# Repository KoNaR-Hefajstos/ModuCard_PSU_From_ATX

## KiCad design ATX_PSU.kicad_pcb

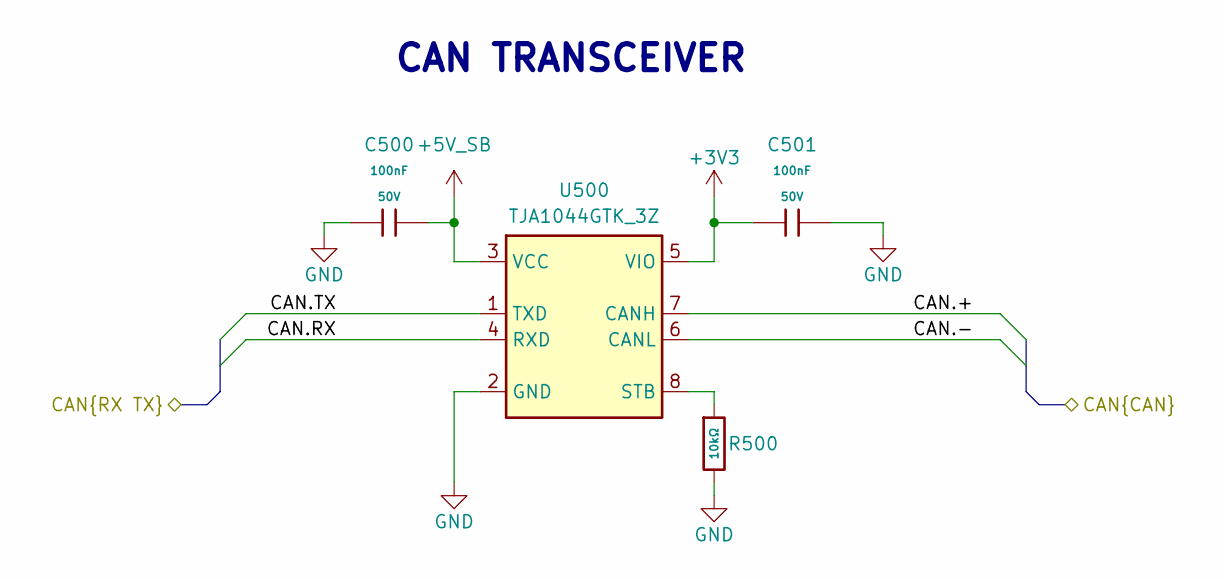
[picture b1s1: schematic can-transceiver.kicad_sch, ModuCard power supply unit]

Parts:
C500, C501: 100nF; C_0402; Voltage Rated 50V; Tolerance ±10%; Part CL05B104KB54PNC; LCSC C307331
R500: 10kΩ; R_0402; Overload Voltage (Max) 50V; Tolerance ±1%; Part 0402WGF1002TCE; LCSC C25744
U500: TJA1044GTK_3Z; HVSON-8-1EP_3x3mm_P0.65mm_EP1.6x2.4mm; Manufacturer_Part_Number TJA1044GTK/3Z; LCSC C5215851

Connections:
+3V3: C501.1, U500.5 (VIO); also elsewhere on the board
+5V_SB: C500.2, U500.3 (VCC); also elsewhere on the board
/Backplane/CAN1.+: U500.7 (CANH); also elsewhere on the board
/Backplane/CAN1.-: U500.6 (CANL); also elsewhere on the board
/CAN transceiver 1/CAN.RX: U500.4 (RXD); also elsewhere on the board
/CAN transceiver 1/CAN.TX: U500.1 (TXD); also elsewhere on the board
GND: C500.1, C501.2, R500.2, U500.2 (GND), U500.9 (EP); also elsewhere on the board
unnamed: R500.1, U500.8 (STB)

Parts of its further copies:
C600, C601: 100nF; C_0402; Voltage Rated 50V; Tolerance ±10%; Part CL05B104KB54PNC; LCSC C307331
R600: 10kΩ; R_0402; Overload Voltage (Max) 50V; Tolerance ±1%; Part 0402WGF1002TCE; LCSC C25744
U600: TJA1044GTK_3Z; HVSON-8-1EP_3x3mm_P0.65mm_EP1.6x2.4mm; Manufacturer_Part_Number TJA1044GTK/3Z; LCSC C5215851

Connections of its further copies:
+3V3: C601.1, U600.5 (VIO); also elsewhere on the board
+5V_SB: C600.2, U600.3 (VCC); also elsewhere on the board
/Backplane/CAN2.+: U600.7 (CANH); also elsewhere on the board
/Backplane/CAN2.-: U600.6 (CANL); also elsewhere on the board
/CAN transceiver 2/CAN.RX: U600.4 (RXD); also elsewhere on the board
/CAN transceiver 2/CAN.TX: U600.1 (TXD); also elsewhere on the board
GND: C600.1, C601.2, R600.2, U600.2 (GND), U600.9 (EP); also elsewhere on the board
unnamed: R600.1, U600.8 (STB)

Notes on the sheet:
CAN TRANSCEIVER

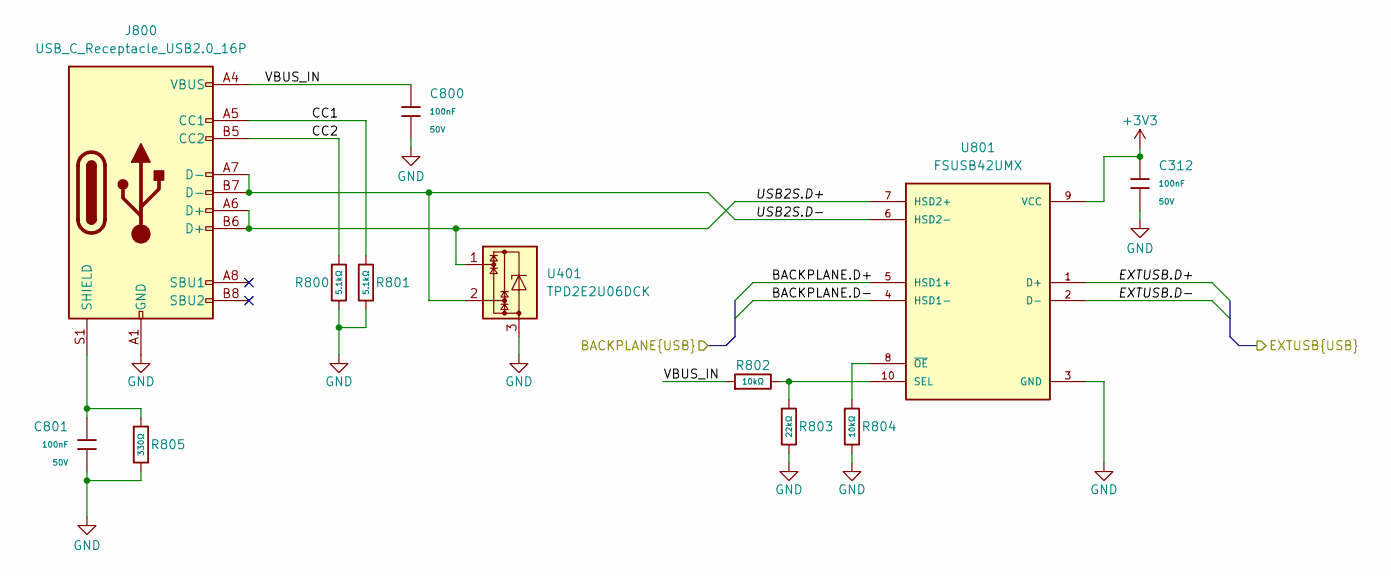
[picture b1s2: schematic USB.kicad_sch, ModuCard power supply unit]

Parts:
C312, C800, C801: 100nF; C_0402; Voltage Rated 50V; Tolerance ±10%; Part CL05B104KB54PNC; LCSC C307331
J800: USB_C_Receptacle_USB2.0_16P; USB_C_Receptacle_GCT_USB4105-xx-A_16P_TopMnt_Horizontal
R800, R801: 5.1kΩ; R_0402; Overload Voltage (Max) 50V; Tolerance ±1%; Part 0402WGF5101TCE; LCSC C25905
R802, R804: 10kΩ; R_0402; Overload Voltage (Max) 50V; Tolerance ±1%; Part 0402WGF1002TCE; LCSC C25744
R803: 22kΩ; R_0402; Overload Voltage (Max) 50V; Tolerance ±1%; Part 0402WGF2202TCE; LCSC C25768
R805: 330Ω; R_0402; Overload Voltage (Max) 50V; Tolerance ±1%; Part 0402WGF3300TCE; LCSC C25104
U401: TPD2E2U06DCK; SOT-323_SC-70; LCSC C5350871
U801: FSUSB42UMX; UFQFN-10_1.4x1.8; PARTREV 1.25; LCSC C49186231

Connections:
+3V3: C312.1, U801.9 (VCC); also elsewhere on the board
/Backplane/BACKPLANE.D+: U801.5 (HSD1+); also elsewhere on the board
/Backplane/BACKPLANE.D-: U801.4 (HSD1-); also elsewhere on the board
/USB-hub/USBIN1.D+: U801.1 (D+); also elsewhere on the board
/USB-hub/USBIN1.D-: U801.2 (D-); also elsewhere on the board
/USB/CC1: J800.A5 (CC1), R801.1
/USB/CC2: J800.B5 (CC2), R800.1
/USB/USB2S.D+: J800.A6 (D+), J800.B6 (D+), U401.1, U801.7 (HSD2+)
/USB/USB2S.D-: J800.A7 (D-), J800.B7 (D-), U401.2, U801.6 (HSD2-)
/USB/VBUS_IN: C800.1, J800.A4 (VBUS), J800.A9 (VBUS), J800.B4 (VBUS), J800.B9 (VBUS), R802.1
GND: C312.2, C800.2, C801.2, J800.A1 (GND), J800.A12 (GND), J800.B1 (GND), J800.B12 (GND), R800.2, R801.2, R803.2, R804.2, R805.2, U401.3, U801.3 (GND); also elsewhere on the board
unnamed: C801.1, J800.S1 (SHIELD), R805.1
unnamed: R802.2, R803.1, U801.10 (SEL)
unnamed: R804.1, U801.8 (~OE)

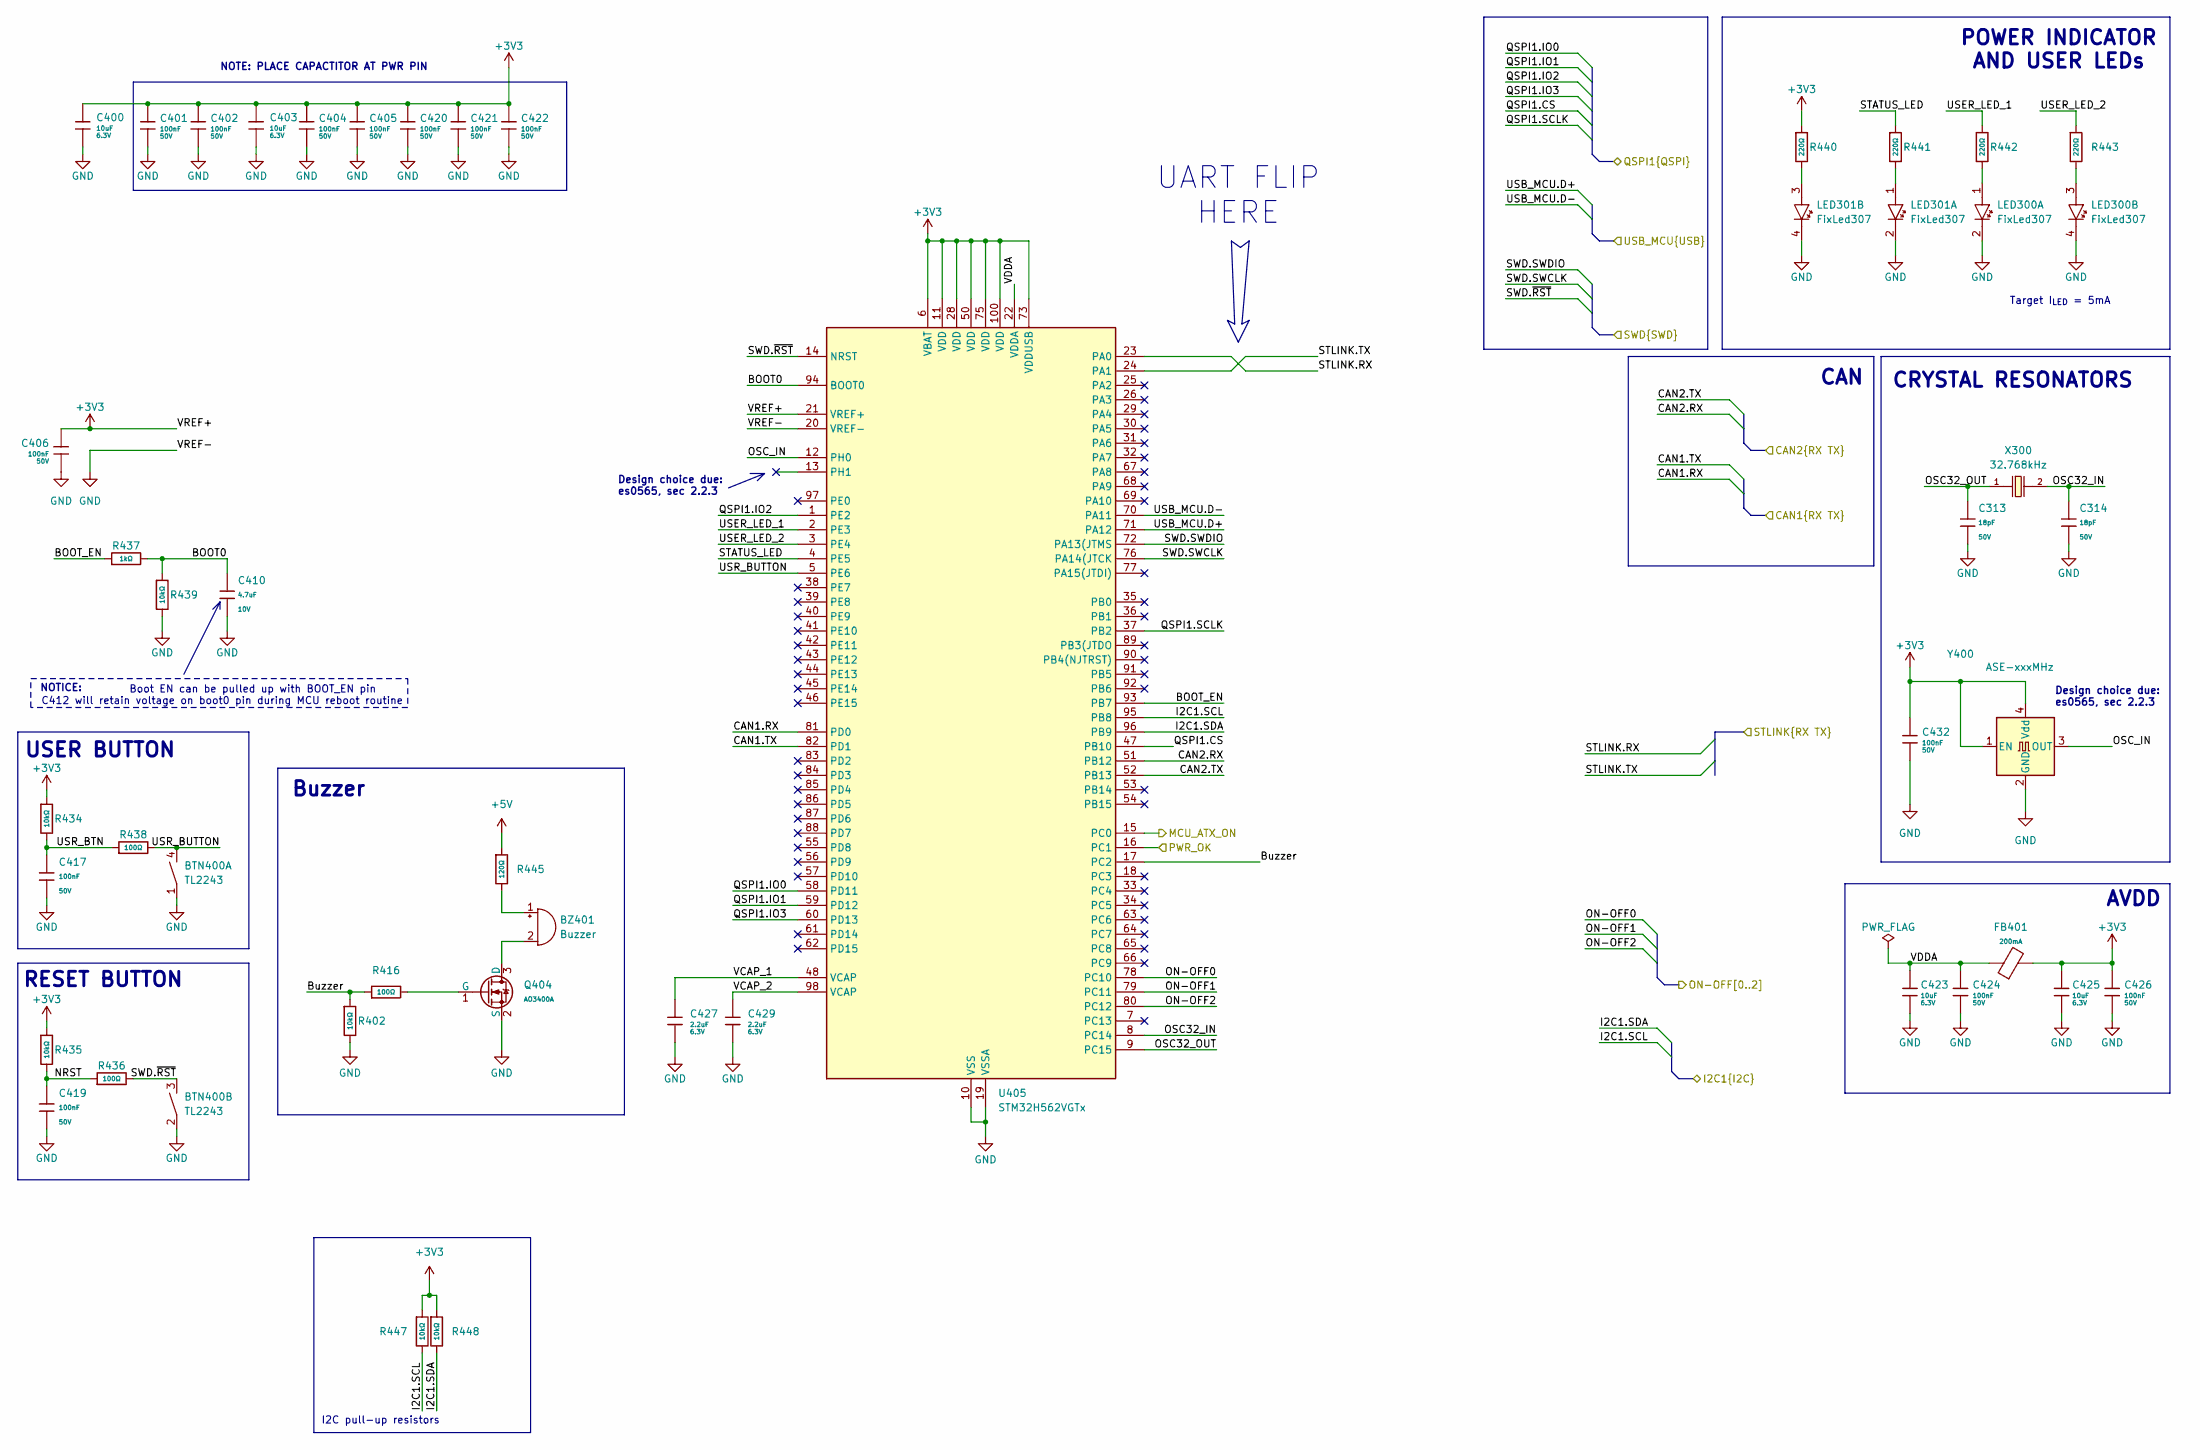
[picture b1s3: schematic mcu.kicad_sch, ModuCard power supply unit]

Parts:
BTN400: TL2243
BZ401: Buzzer; BUZ-TH_BD12.0-P7.60-D0.6-FD
C313, C314: 18pF; C_0402; Voltage Rated 50V; Tolerance ±5%; Part 0402CG180J500NT; LCSC C1549
C400, C403, C423, C425: 10uF; C_0402; Voltage Rated 6.3V; Tolerance ±20%; Part CL05A106MQ5NUNC; LCSC C15525
C401, C402, C404, C405, C406, C417, C419, C420, C421, C422, C424, C426, C432: 100nF; C_0402; Voltage Rated 50V; Tolerance ±10%; Part CL05B104KB54PNC; LCSC C307331
C410: 4.7uF; C_0402; Voltage Rated 10V; Tolerance ±20%; Part CL05A475MP5NRNC; LCSC C23733
C427, C429: 2.2uF; C_0402; Voltage Rated 6.3V; Tolerance ±20%; Part CL05A225MQ5NSNC; LCSC C12530
FB401: FB_0603; Current Rating 200mA; Tolerance ±25%; Part GZ1608D601TF; LCSC C1002
LED300, LED301: FixLed307
Q404: AO3400A; Q_SOT-23; Part AO3400A; LCSC C20917
R402, R434, R435, R439, R447, R448: 10kΩ; R_0402; Overload Voltage (Max) 50V; Tolerance ±1%; Part 0402WGF1002TCE; LCSC C25744
R416: 100Ω; R_0603; Overload Voltage (Max) 75V; Tolerance ±1%; Part 0603WAF1000T5E; LCSC C22775
R436, R438: 100Ω; R_0402; Overload Voltage (Max) 50V; Tolerance ±1%; Part 0402WGF1000TCE; LCSC C25076
R437: 1kΩ; R_0402; Overload Voltage (Max) 50V; Tolerance ±1%; Part 0402WGF1001TCE; LCSC C11702
R440, R441, R442, R443: 220Ω; R_0402; Overload Voltage (Max) 50V; Tolerance ±1%; Part 0402WGF2200TCE; LCSC C25091
R445: 120Ω; R_0402; Overload Voltage (Max) 50V; Tolerance ±1%; Part 0402WGF1200TCE; LCSC C25079
U405: STM32H562VGTx; LQFP-100_14x14mm_P0.5mm
X300: Q13FC1350000400; FC-135R_L3.2-W1.5; Frequency Tolerance ±20ppm; Part Q13FC13500004; LCSC C32346
Y400: ASE-xxxMHz; Oscillator_SMD_Abracon_ASE-4Pin_3.2x2.5mm; MPN OT322512MJBA4SL; LCSC C725989

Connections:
+3V3: C400.1, C401.1, C402.1, C403.1, C404.1, C405.1, C406.1, C420.1, C421.1, C422.1, C425.1, C426.1, C432.1, FB401.2, R434.1, R435.1, R440.1, R447.1, R448.1, U405.6 (VBAT), U405.11 (VDD), U405.21 (VREF+), U405.28 (VDD), U405.50 (VDD), U405.73 (VDDUSB), U405.75 (VDD), U405.100 (VDD), Y400.1 (EN), Y400.4 (Vdd); also elsewhere on the board
+5V: R445.1; also elsewhere on the board
/ATX connector/PWR_OK_ATX: U405.16 (PC1); also elsewhere on the board
/CAN transceiver 1/CAN.RX: U405.81 (PD0); also elsewhere on the board
/CAN transceiver 1/CAN.TX: U405.82 (PD1); also elsewhere on the board
/CAN transceiver 2/CAN.RX: U405.51 (PB12); also elsewhere on the board
/CAN transceiver 2/CAN.TX: U405.52 (PB13); also elsewhere on the board
/MCU/BOOT0: C410.1, R437.2, R439.1, U405.94 (BOOT0)
/MCU/BOOT_EN: R437.1, U405.93 (PB7)
/MCU/Buzzer: R402.1, R416.1, U405.17 (PC2)
/MCU/I2C1.SCL: R447.2, U405.95 (PB8); also elsewhere on the board
/MCU/I2C1.SDA: R448.2, U405.96 (PB9); also elsewhere on the board
/MCU/MCU_ATX_ON: U405.15 (PC0); also elsewhere on the board
/MCU/NRST: C419.1, R435.2, R436.1
/MCU/ON-OFF0: U405.78 (PC10); also elsewhere on the board
/MCU/ON-OFF1: U405.79 (PC11); also elsewhere on the board
/MCU/ON-OFF2: U405.80 (PC12); also elsewhere on the board
/MCU/OSC32_IN: C314.1, U405.8 (PC14), X300.2
/MCU/OSC32_OUT: C313.1, U405.9 (PC15), X300.1
/MCU/OSC_IN: U405.12 (PH0), Y400.3 (OUT)
/MCU/QSPI1.CS: U405.47 (PB10); also elsewhere on the board
/MCU/QSPI1.IO0: U405.58 (PD11); also elsewhere on the board
/MCU/QSPI1.IO1: U405.59 (PD12); also elsewhere on the board
/MCU/QSPI1.IO2: U405.1 (PE2); also elsewhere on the board
/MCU/QSPI1.IO3: U405.60 (PD13); also elsewhere on the board
/MCU/QSPI1.SCLK: U405.37 (PB2); also elsewhere on the board
/MCU/STATUS_LED: R441.1, U405.4 (PE5)
/MCU/STLINK.RX: U405.23 (PA0); also elsewhere on the board
/MCU/STLINK.TX: U405.24 (PA1); also elsewhere on the board
/MCU/SWD.SWCLK: U405.76 (PA14(JTCK); also elsewhere on the board
/MCU/SWD.SWDIO: U405.72 (PA13(JTMS); also elsewhere on the board
/MCU/SWD.~RST: BTN400.3, R436.2, U405.14 (NRST); also elsewhere on the board
/MCU/USB_MCU.D+: U405.71 (PA12); also elsewhere on the board
/MCU/USB_MCU.D-: U405.70 (PA11); also elsewhere on the board
/MCU/USER_LED_1: R442.1, U405.2 (PE3)
/MCU/USER_LED_2: R443.1, U405.3 (PE4)
/MCU/USR_BTN: C417.1, R434.2, R438.1
/MCU/USR_BUTTON: BTN400.4, R438.2, U405.5 (PE6)
/MCU/VCAP_1: C427.1, U405.48 (VCAP)
/MCU/VCAP_2: C429.1, U405.98 (VCAP)
/MCU/VDDA: C423.1, C424.1, FB401.1, U405.22 (VDDA)
GND: BTN400.1, BTN400.2, C313.2, C314.2, C400.2, C401.2, C402.2, C403.2, C404.2, C405.2, C406.2, C410.2, C417.2, C419.2, C420.2, C421.2, C422.2, C423.2, C424.2, C425.2, C426.2, C427.2, C429.2, C432.2, LED300.2, LED300.4, LED301.2, LED301.4, Q404.2 (S), R402.2, R439.2, U405.10 (VSS), U405.19 (VSSA), U405.20 (VREF-), U405.27 (VSS), U405.49 (VSS), U405.74 (VSS), U405.99 (VSS), Y400.2 (GND); also elsewhere on the board
unnamed: BZ401.1 (+), R445.2
unnamed: BZ401.2 (-), Q404.3 (D)
unnamed: LED300.1, R442.2
unnamed: LED300.3, R443.2
unnamed: LED301.1, R441.2
unnamed: LED301.3, R440.2
unnamed: Q404.1 (G), R416.2

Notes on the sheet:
Design choice due: es0565, sec 2.2.3
USER BUTTON
AVDD
CRYSTAL RESONATORS
RESET BUTTON
Buzzer
NOTICE:
POWER INDICATOR AND USER LEDs
Target I_{LED} = 5mA
I2C pull-up resistors
CAN
Boot EN can be pulled up with BOOT_EN pin C412 will retain voltage on boot0 pin during MCU reboot routine
UART FLIP HERE
NOTE: PLACE CAPACTITOR AT PWR PIN

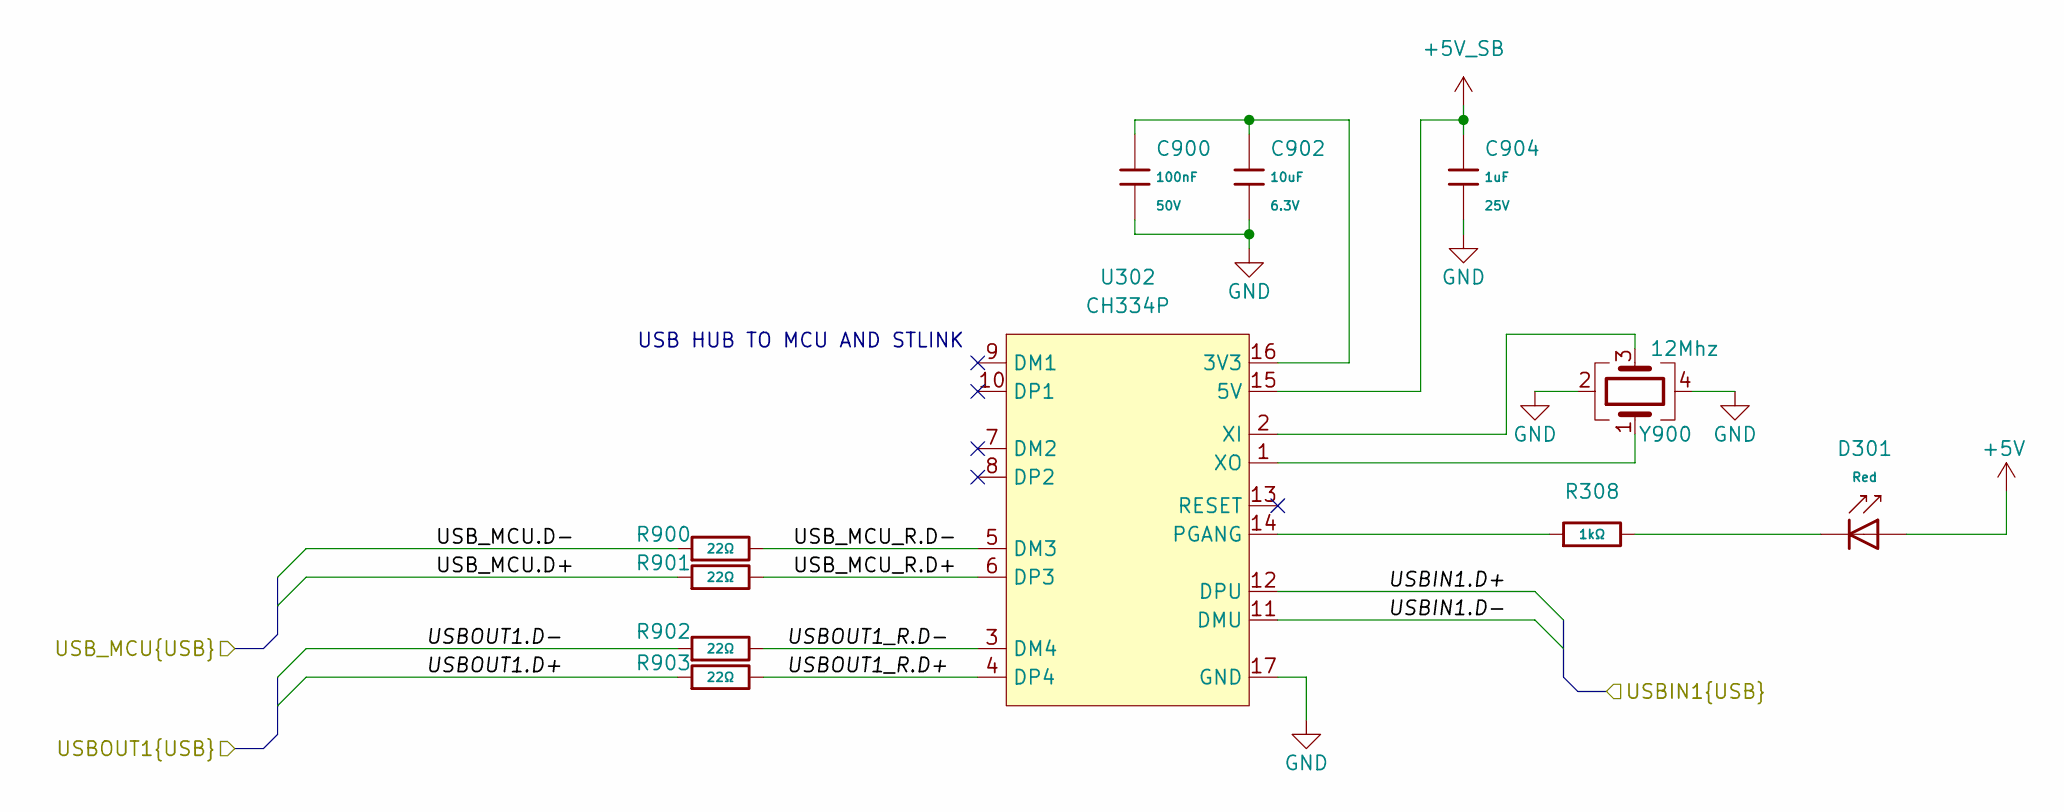
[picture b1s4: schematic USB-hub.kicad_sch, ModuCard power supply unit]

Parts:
C900: 100nF; C_0402; Voltage Rated 50V; Tolerance ±10%; Part CL05B104KB54PNC; LCSC C307331
C902: 10uF; C_0402; Voltage Rated 6.3V; Tolerance ±20%; Part CL05A106MQ5NUNC; LCSC C15525
C904: 1uF; C_0402; Voltage Rated 25V; Tolerance ±10%; Part CL05A105KA5NQNC; LCSC C52923
D301: Red; D_0603; Part KT-0603R; LCSC C2286
R308: 1kΩ; R_0402; Overload Voltage (Max) 50V; Tolerance ±1%; Part 0402WGF1001TCE; LCSC C11702
R900, R901, R902, R903: 22Ω; R_0402; Overload Voltage (Max) 50V; Tolerance ±1%; Part 0402WGF220JTCE; LCSC C25092
U302: CH334P; QFN-16-1EP_3x3mm_P0.5mm_EP1.7x1.7mm; LCSC C5373042
Y900: 12Mhz; Crystal_SMD_3225-4Pin_3.2x2.5mm; LCSC C70565

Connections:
+5V: D301.2; also elsewhere on the board
+5V_SB: C904.1, U302.15 (5V); also elsewhere on the board
/MCU/USB_MCU.D+: R901.1; also elsewhere on the board
/MCU/USB_MCU.D-: R900.1; also elsewhere on the board
/ST-LINK/ST-LINK.D+: R903.1; also elsewhere on the board
/ST-LINK/ST-LINK.D-: R902.1; also elsewhere on the board
/USB-hub/USBIN1.D+: U302.12 (DPU); also elsewhere on the board
/USB-hub/USBIN1.D-: U302.11 (DMU); also elsewhere on the board
/USB-hub/USBOUT1_R.D+: R903.2, U302.4 (DP4)
/USB-hub/USBOUT1_R.D-: R902.2, U302.3 (DM4)
/USB-hub/USB_MCU_R.D+: R901.2, U302.6 (DP3)
/USB-hub/USB_MCU_R.D-: R900.2, U302.5 (DM3)
GND: C900.2, C902.2, C904.2, U302.17 (GND), Y900.2, Y900.4; also elsewhere on the board
unnamed: D301.1, R308.2
unnamed: C900.1, C902.1, U302.16 (3V3)
unnamed: R308.1, U302.14 (PGANG)
unnamed: U302.2 (XI), Y900.3
unnamed: U302.1 (XO), Y900.1

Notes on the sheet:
USB HUB TO MCU AND STLINK

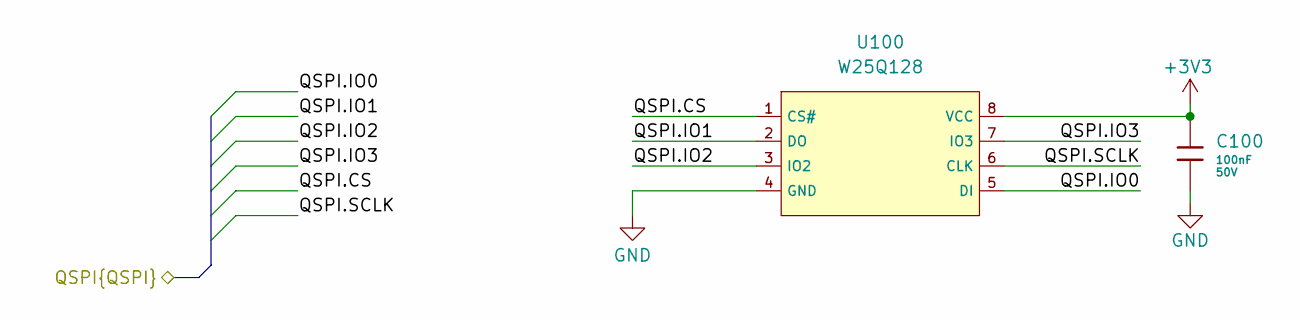
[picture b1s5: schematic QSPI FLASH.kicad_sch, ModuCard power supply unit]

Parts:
C100: 100nF; C_0402; Voltage Rated 50V; Tolerance ±10%; Part CL05B104KB54PNC; LCSC C307331
U100: W25Q128; SOIC-8_L5.3-W5.3-P1.27-LS8.0-BL; Part W25Q128JVSIQ; LCSC C97521

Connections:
+3V3: C100.1, U100.8 (VCC); also elsewhere on the board
/MCU/QSPI1.CS: U100.1 (CS#); also elsewhere on the board
/MCU/QSPI1.IO0: U100.5 (DI); also elsewhere on the board
/MCU/QSPI1.IO1: U100.2 (DO); also elsewhere on the board
/MCU/QSPI1.IO2: U100.3 (IO2); also elsewhere on the board
/MCU/QSPI1.IO3: U100.7 (IO3); also elsewhere on the board
/MCU/QSPI1.SCLK: U100.6 (CLK); also elsewhere on the board
GND: C100.2, U100.4 (GND); also elsewhere on the board

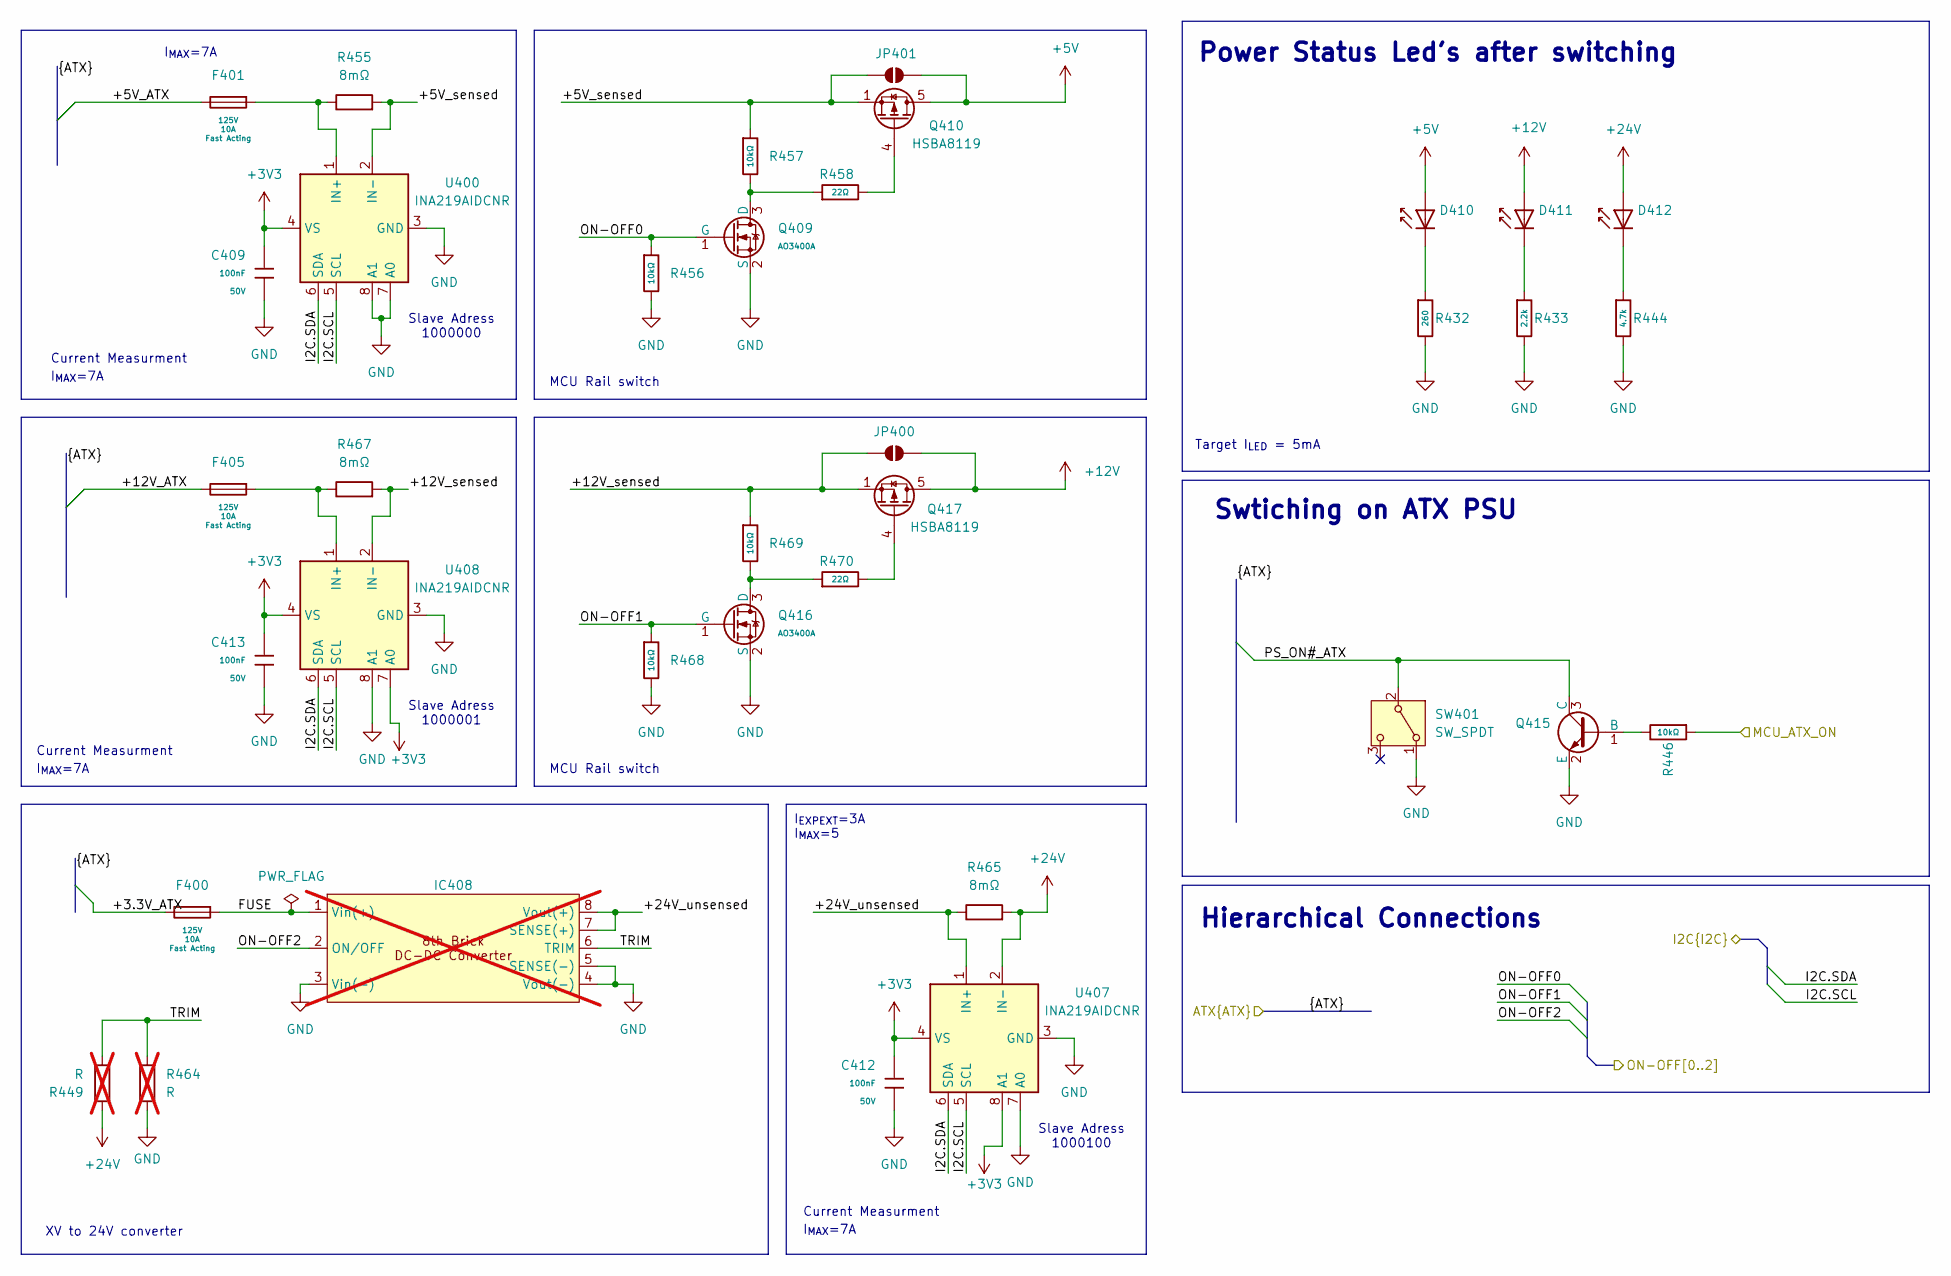
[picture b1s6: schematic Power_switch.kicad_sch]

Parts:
C409, C412, C413: 100nF; C_0402; Voltage Rated 50V; Tolerance ±10%; Part CL05B104KB54PNC; LCSC C307331
D410, D411, D412: Green; D_0603; Part 19-217/GHC-YR1S2/6T; LCSC C2986059
F400, F401, F405: 10A; Fuse_2410_6125; Voltage Rating 125V; LCSC C136374
IC408: 8th DC-DC converter; not fitted
JP400, JP401: SolderJumper_2_Open; SolderJumper-2_P1.3mm_Open_RoundedPad1.0x1.5mm
Q409, Q416: AO3400A; Q_SOT-23; Part AO3400A; LCSC C20917
Q410, Q417: HSBA8119; DFN5060-8L; LCSC C22359243
Q415: MMBT5551; Q_SOT-23; Part MMBT5551; LCSC C408396
R432: 260; R_0402; Overload Voltage (Max) 50V; Tolerance ±1%; Part 0402WGF1002TCE; LCSC C25744
R433: 2.2k; R_0402; Overload Voltage (Max) 50V; Tolerance ±1%; Part 0402WGF1002TCE; LCSC C25744
R444: 4.7k; R_0402; Overload Voltage (Max) 50V; Tolerance ±1%; Part 0402WGF1002TCE; LCSC C25744
R446, R456, R457, R468, R469: 10kΩ; R_0402; Overload Voltage (Max) 50V; Tolerance ±1%; Part 0402WGF1002TCE; LCSC C25744
R449, R464: R; R_0402; not fitted
R455, R465, R467: 8mΩ; R_0805; LCSC C510284
R458, R470: 22Ω; R_0402; Overload Voltage (Max) 50V; Tolerance ±1%; Part 0402WGF220JTCE; LCSC C25092
SW401: SW_SPDT; SW_Slide-03_Wuerth-WS-SLTV_10x2.5x6.4_P2.54mm
U400, U407, U408: INA219AIDCNR; SOT-23-8; LCSC C87469

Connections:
+3V3: C409.1, C412.1, C413.1, U400.4 (VS), U407.4 (VS), U407.8 (A1), U408.4 (VS), U408.7 (A0); also elsewhere on the board
+5V: D410.2, JP401.2 (B), Q410.5, Q410.6, Q410.7, Q410.8, Q410.9; also elsewhere on the board
+12V: D411.2, JP400.2 (B), Q417.5, Q417.6, Q417.7, Q417.8, Q417.9; also elsewhere on the board
+24V: D412.2, R449.1, R465.2, U407.2 (IN-); also elsewhere on the board
/ATX connector/+3.3V_ATX: F400.2; also elsewhere on the board
/ATX connector/+5V_ATX: F401.2; also elsewhere on the board
/ATX connector/+12V_ATX: F405.2; also elsewhere on the board
/ATX connector/PS_ON#_ATX: Q415.3 (C), SW401.2 (B); also elsewhere on the board
/MCU/I2C1.SCL: U400.5 (SCL), U407.5 (SCL), U408.5 (SCL); also elsewhere on the board
/MCU/I2C1.SDA: U400.6 (SDA), U407.6 (SDA), U408.6 (SDA); also elsewhere on the board
/MCU/MCU_ATX_ON: R446.1; also elsewhere on the board
/MCU/ON-OFF0: Q409.1 (G), R456.1; also elsewhere on the board
/MCU/ON-OFF1: Q416.1 (G), R468.1; also elsewhere on the board
/MCU/ON-OFF2: IC408.2 (ON/OFF); also elsewhere on the board
/Power_switch/+5V_sensed: JP401.1 (A), Q410.1, Q410.2, Q410.3, R455.2, R457.1, U400.2 (IN-)
/Power_switch/+12V_sensed: JP400.1 (A), Q417.1, Q417.2, Q417.3, R467.2, R469.1, U408.2 (IN-)
/Power_switch/+24V_unsensed: IC408.7 (SENSE(+)), IC408.8 (Vout(+)), R465.1, U407.1 (IN+)
/Power_switch/FUSE: F400.1, IC408.1 (Vin(+))
/Power_switch/TRIM: IC408.6 (TRIM), R449.2, R464.2
GND: C409.2, C412.2, C413.2, IC408.3 (Vin(-)), IC408.4 (Vout(-)), IC408.5 (SENSE(-)), Q409.2 (S), Q415.2 (E), Q416.2 (S), R432.2, R433.2, R444.2, R456.2, R464.1, R468.2, SW401.1 (A), U400.3 (GND), U400.7 (A0), U400.8 (A1), U407.3 (GND), U407.7 (A0), U408.3 (GND), U408.8 (A1); also elsewhere on the board
unnamed: D410.1, R432.1
unnamed: D411.1, R433.1
unnamed: D412.1, R444.1
unnamed: Q409.3 (D), R457.2, R458.1
unnamed: Q410.4, R458.2
unnamed: Q415.1 (B), R446.2
unnamed: Q416.3 (D), R469.2, R470.1
unnamed: Q417.4, R470.2
unnamed: F401.1, R455.1, U400.1 (IN+)
unnamed: F405.1, R467.1, U408.1 (IN+)

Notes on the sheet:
I_{MAX}=7A
Slave Adress 1000100
Slave Adress 1000001
Slave Adress 1000000
I_{EXPEXT}=3A I_{MAX}=5
MCU Rail switch
Target I_{LED} = 5mA
Current Measurment
Power Status Led's after switching
Hierarchical Connections
Swtiching on ATX PSU
XV to 24V converter

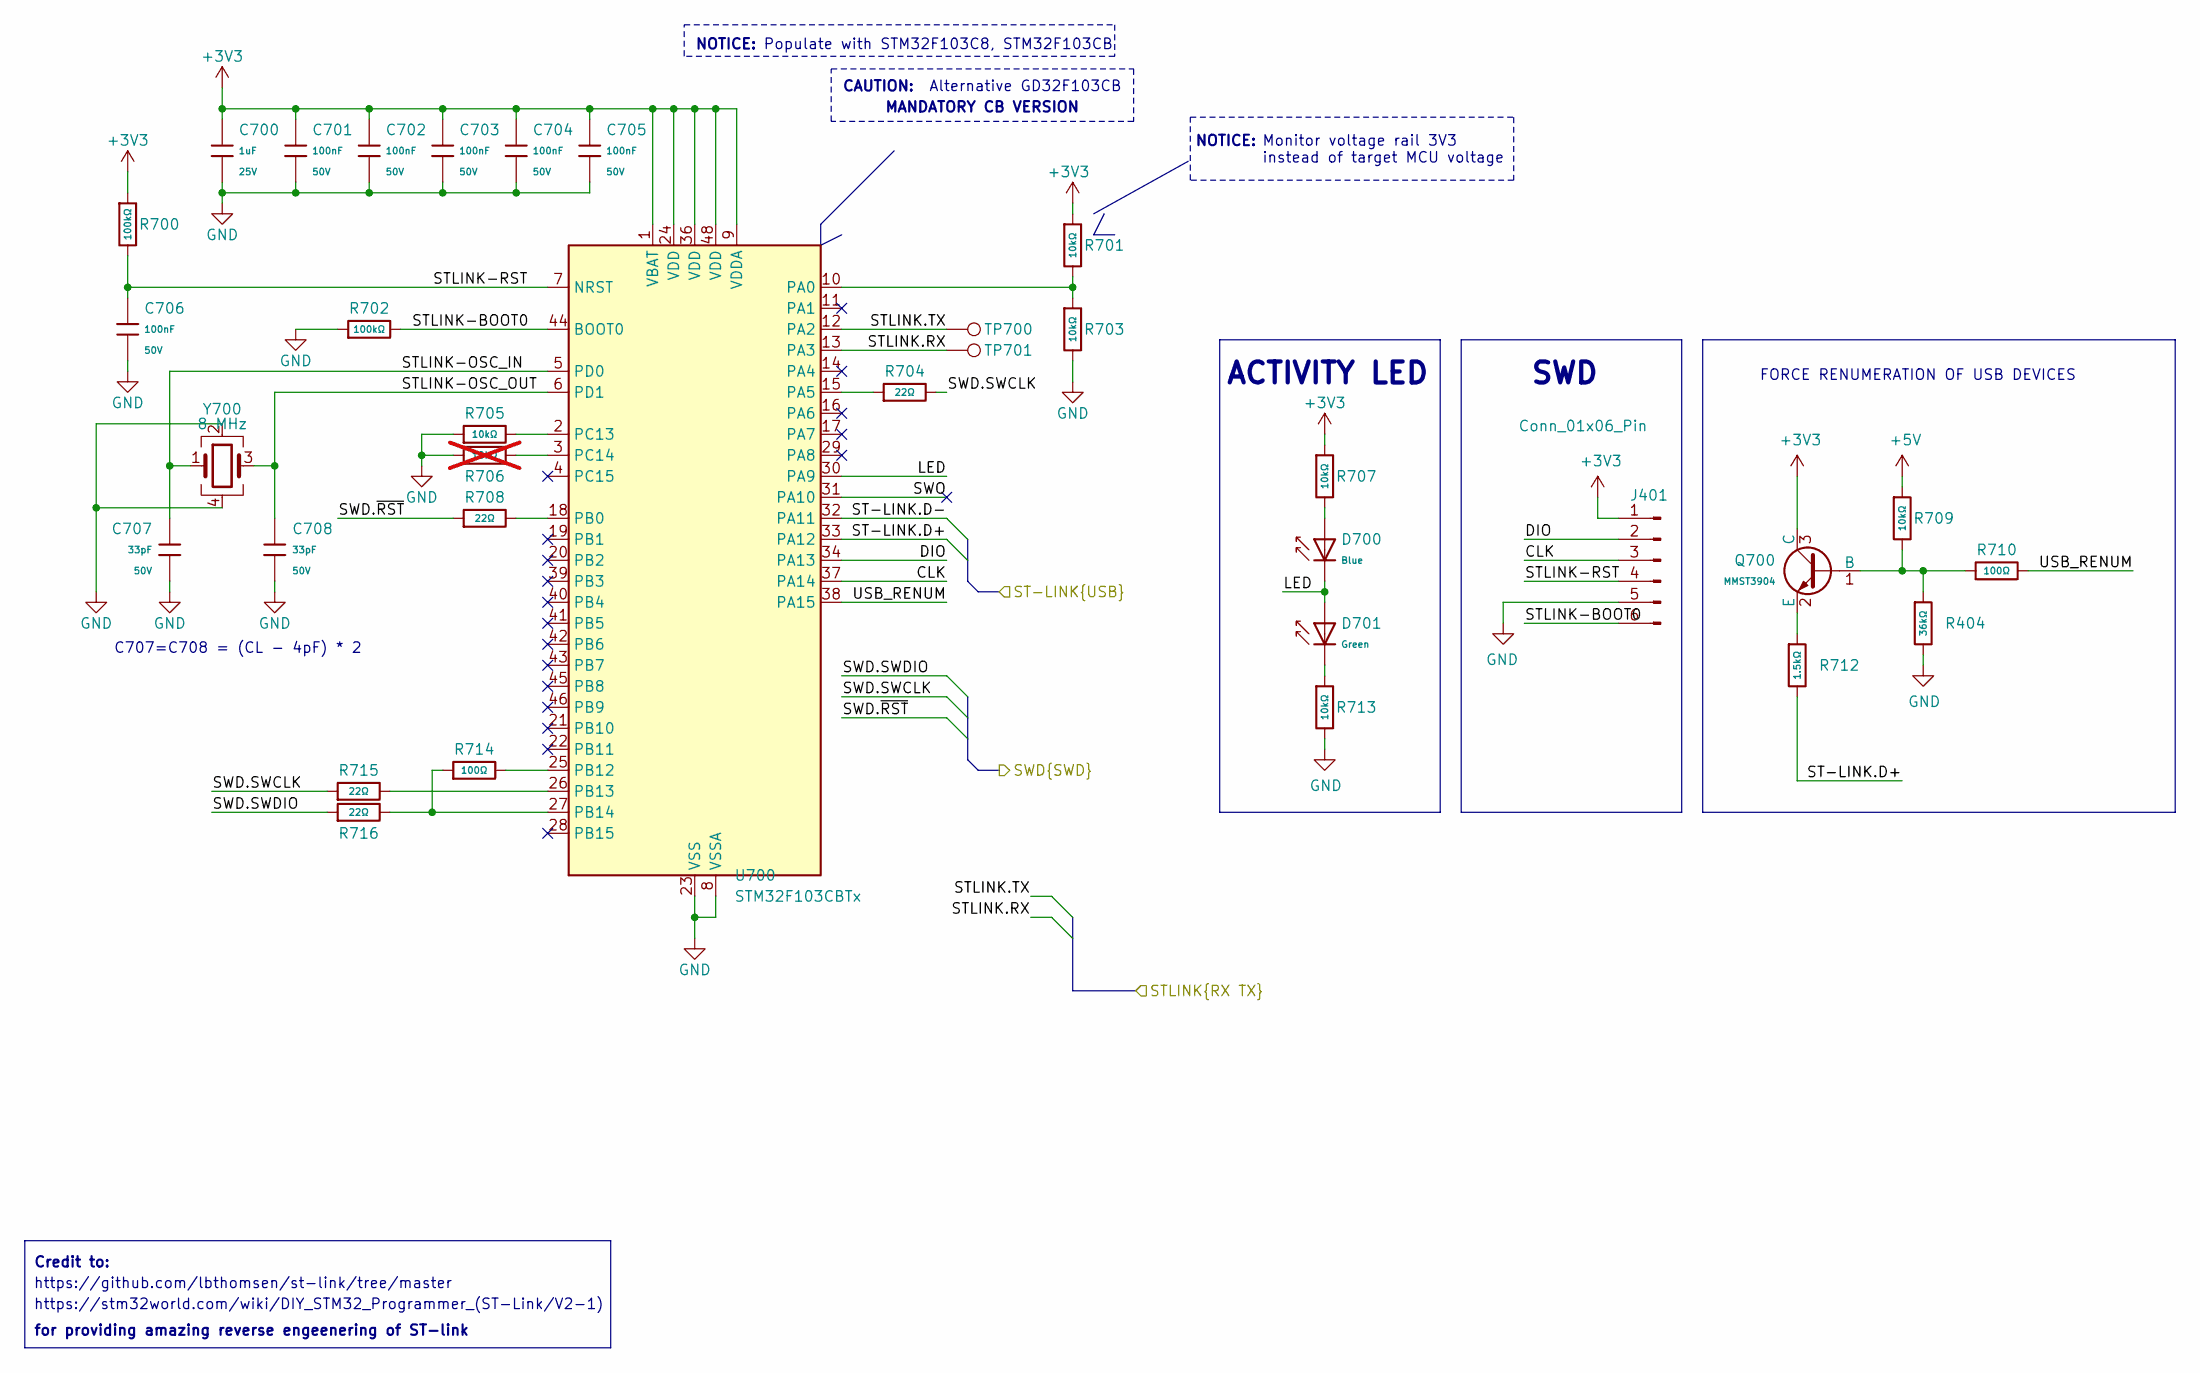
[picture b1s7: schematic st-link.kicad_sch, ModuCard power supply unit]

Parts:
C700: 1uF; C_0402; Voltage Rated 25V; Tolerance ±10%; Part CL05A105KA5NQNC; LCSC C52923
C701, C702, C703, C704, C705, C706: 100nF; C_0402; Voltage Rated 50V; Tolerance ±10%; Part CL05B104KB54PNC; LCSC C307331
C707, C708: 33pF; C_0402; Voltage Rated 50V; Tolerance ±5%; Part 0402CG330J500NT; LCSC C1562
D700: Blue; D_0603; Part 19-217/BHC-ZL1M2RY/6T; LCSC C2986058
D701: Green; D_0603; Part 19-217/GHC-YR1S2/6T; LCSC C2986059
J401: Conn_01x06_Pin; PinHeader_1x06_P1.27mm_Vertical
Q700: MMST3904; Q_SOT-323; Part MMST3904; LCSC C22388837
R404: 36kΩ; R_0603; Overload Voltage (Max) 75V; Tolerance ±1%; Part 0603WAF3602T5E; LCSC C23147
R700, R702: 100kΩ; R_0402; Overload Voltage (Max) 50V; Tolerance ±1%; Part 0402WGF1003TCE; LCSC C25741
R701, R703, R705, R707, R709, R713: 10kΩ; R_0402; Overload Voltage (Max) 50V; Tolerance ±1%; Part 0402WGF1002TCE; LCSC C25744
R704, R708, R715, R716: 22Ω; R_0402; Overload Voltage (Max) 50V; Tolerance ±1%; Part 0402WGF220JTCE; LCSC C25092
R706: 10kΩ; R_0402; Overload Voltage (Max) 50V; Tolerance ±1%; Part 0402WGF1002TCE; LCSC C25744; not fitted
R710, R714: 100Ω; R_0402; Overload Voltage (Max) 50V; Tolerance ±1%; Part 0402WGF1000TCE; LCSC C25076
R712: 1.5kΩ; R_0402; Overload Voltage (Max) 50V; Tolerance ±1%; Part 0402WGF1501TCE; LCSC C25867
TP700, TP701: TestPoint; TestPoint_Pad_D1.0mm
U700: STM32F103CBTx; LQFP-48_7x7mm_P0.5mm
Y700: 8 MHz; CRYSTAL-SMD_4P-L3.2-W2.5-BL; MPN 3225-8.00-20-10-10/4B; LCSC C2682775

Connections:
+3V3: C700.1, C701.1, C702.1, C703.1, C704.1, C705.1, J401.1, Q700.3 (C), R700.1, R701.1, R707.1, U700.1 (VBAT), U700.9 (VDDA), U700.24 (VDD), U700.36 (VDD), U700.48 (VDD); also elsewhere on the board
+5V: R709.1; also elsewhere on the board
/MCU/STLINK.RX: TP701.1, U700.13 (PA3); also elsewhere on the board
/MCU/STLINK.TX: TP700.1, U700.12 (PA2); also elsewhere on the board
/MCU/SWD.SWCLK: R704.2, R715.1; also elsewhere on the board
/MCU/SWD.SWDIO: R716.1; also elsewhere on the board
/MCU/SWD.~RST: R708.1; also elsewhere on the board
/ST-LINK/CLK: J401.3, U700.37 (PA14)
/ST-LINK/DIO: J401.2, U700.34 (PA13)
/ST-LINK/LED: D700.1, D701.2, U700.30 (PA9)
/ST-LINK/ST-LINK.D+: R712.2, U700.33 (PA12); also elsewhere on the board
/ST-LINK/ST-LINK.D-: U700.32 (PA11); also elsewhere on the board
/ST-LINK/STLINK-BOOT0: J401.6, R702.2, U700.44 (BOOT0)
/ST-LINK/STLINK-OSC_IN: C707.1, U700.5 (PD0), Y700.1
/ST-LINK/STLINK-OSC_OUT: C708.1, U700.6 (PD1), Y700.3
/ST-LINK/STLINK-RST: C706.1, J401.4, R700.2, U700.7 (NRST)
/ST-LINK/SWO: U700.31 (PA10)
/ST-LINK/USB_RENUM: R710.2, U700.38 (PA15)
GND: C700.2, C701.2, C702.2, C703.2, C704.2, C705.2, C706.2, C707.2, C708.2, J401.5, R404.2, R702.1, R703.2, R705.1, R706.1, R713.2, U700.8 (VSSA), U700.23 (VSS), U700.35 (VSS), U700.47 (VSS), Y700.2, Y700.4; also elsewhere on the board
unnamed: D700.2, R707.2
unnamed: D701.1, R713.1
unnamed: Q700.1 (B), R404.1, R709.2, R710.1
unnamed: Q700.2 (E), R712.1
unnamed: R701.2, R703.1, U700.10 (PA0)
unnamed: R704.1, U700.15 (PA5)
unnamed: R708.2, U700.18 (PB0)
unnamed: R714.2, U700.25 (PB12)
unnamed: R715.2, U700.26 (PB13)
unnamed: R714.1, R716.2, U700.27 (PB14)
unnamed: R705.2, U700.2 (PC13)
unnamed: R706.2, U700.3 (PC14)

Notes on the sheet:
Alternative GD32F103CB
SWD
NOTICE:
C707=C708 = (CL - 4pF) * 2
Monitor voltage rail 3V3 instead of target MCU voltage
https://stm32world.com/wiki/DIY_STM32_Programmer_(ST-Link/V2-1)
CAUTION:
Populate with STM32F103C8, STM32F103CB
ACTIVITY LED
for providing amazing reverse engeenering of ST-link
MANDATORY CB VERSION
FORCE RENUMERATION OF USB DEVICES
https://github.com/lbthomsen/st-link/tree/master
Credit to:
